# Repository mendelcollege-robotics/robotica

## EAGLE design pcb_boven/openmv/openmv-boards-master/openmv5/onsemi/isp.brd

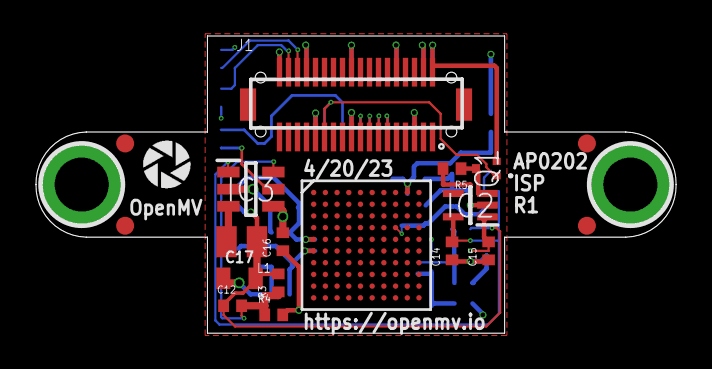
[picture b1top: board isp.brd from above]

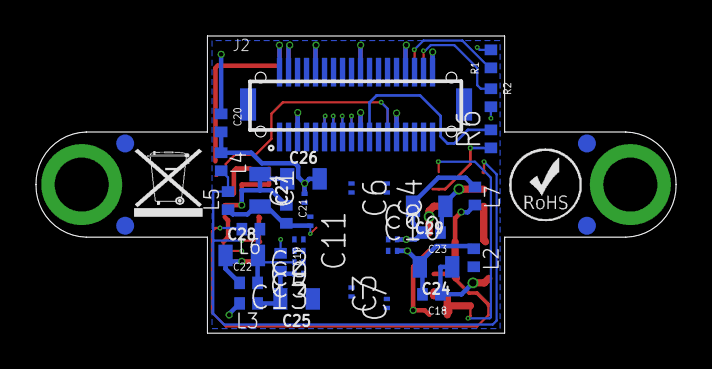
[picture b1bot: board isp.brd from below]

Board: 6 copper layers, 35.6 x 16.5 mm, 61 parts (40 on the bottom side), 56 nets.

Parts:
C1, C2, C3, C4, C5, C6, C7, C8, C9, C10, C11, C13: 0.22uF; C0201
C12: 6.8pF; 0402
C14, C15, C16, C18, C19, C20, C21, C22, C23: 4.7uF; 0402
C17, C24, C25, C26, C27, C28, C29: 22uF; 0805
FD1, FD2, FD3, FD4, FD5, FD6, FD7, FD8: FIDUCIAL1X2; FIDUCIAL-1X2
IC1: AP0202AT2L00XPGA0
IC2: MIC5365-2.8YC5-TR; SOT65P210X110-5N
IC3: TLV62568PDDCR; SOT95P280X110-6N
J1: DF12-36-DS
J2: DF12-36-DP
L1: MAKK2016T2R2M; INDC2016X100N
L2, L3, L4, L5, L6, L7: 100; 0402
M1, M2: 9774030151R
Q1: SSM3J15FV,L3F; SSM3J15FVL3F
R1, R2: 1.5K; R0402
R3, R4, R5: 100K; R0402
R6: 10K; R0402
U$1: WEEE
U$2: ROHS
U$9: OPENMV-LOGO

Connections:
DCMI_CLK: IC1.P$58, J2.12
DCMI_D0: IC1.P$65, J2.31
DCMI_D1: IC1.P$84, J2.29
DCMI_D2: IC1.P$74, J2.35
DCMI_D3: IC1.P$83, J2.28
DCMI_D4: IC1.P$93, J2.26
DCMI_D5: IC1.P$73, J2.33
DCMI_D6: IC1.P$82, J2.24
DCMI_D7: IC1.P$91, J2.22
DCMI_FSIN: IC1.P$63, J2.23
DCMI_HSYNC: IC1.P$64, J2.18
DCMI_MISO: J1.15, J2.15
DCMI_MOSI: J1.17, J2.17
DCMI_PCLK: IC1.P$81, J2.14
DCMI_PWDN: IC1.P$43, J1.25, J2.25, Q1.1
DCMI_PWDN_INT: IC2.3, Q1.3, R5.1
DCMI_RST: J2.21, R6.2
DCMI_SCL: IC1.P$11, J2.32
DCMI_SCLK: J1.13, J2.13
DCMI_SDA: IC1.P$23, J2.34
DCMI_SSEL: J1.11, J2.11
DCMI_VSYNC: IC1.P$72, J2.16
FB: C12.2, IC3.6, R3.1, R4.1
GND: C1.1, C2.1, C3.1, C4.1, C5.1, C6.1, C7.1, C8.1, C9.1, C10.1, C11.1, C13.1, C14.1, C15.1, C16.1, C17.1, C18.1, C19.1, C20.1, C21.1, C22.1, C23.1, C24.1, C25.1, C26.1, C27.1, C28.1, C29.1, IC1.P$1, IC1.P$19, IC1.P$20, IC1.P$22, IC1.P$29, IC1.P$30, IC1.P$32, IC1.P$39, IC1.P$40, IC1.P$44, IC1.P$45, IC1.P$46, IC1.P$48, IC1.P$49, IC1.P$55, IC1.P$56, IC1.P$57, IC1.P$61, IC1.P$69, IC1.P$100, IC2.2, IC3.2, J1.5, J1.19, J1.27, J2.5, J2.19, J2.27, R4.2, R5.2
RESET_N: IC1.P$54, IC3.5, R6.1
SENSOR_CLK: IC1.P$13, J1.12
SENSOR_D0: IC1.P$4, J1.3
SENSOR_D1: IC1.P$15, J1.1
SENSOR_D2: IC1.P$36, J1.9
SENSOR_D3: IC1.P$26, J1.7
SENSOR_D4: IC1.P$16, J1.31
SENSOR_D5: IC1.P$6, J1.29
SENSOR_D6: IC1.P$47, J1.35
SENSOR_D7: IC1.P$37, J1.28
SENSOR_D8: IC1.P$27, J1.26
SENSOR_D9: IC1.P$17, J1.33
SENSOR_D10: IC1.P$7, J1.24
SENSOR_D11: IC1.P$18, J1.22
SENSOR_FSIN: IC1.P$25, J1.23
SENSOR_HSYNC: IC1.P$8, J1.18
SENSOR_PCLK: IC1.P$28, J1.14
SENSOR_RST: IC1.P$35, J1.21
SENSOR_SCL: IC1.P$14, J1.32, R1.1
SENSOR_SDA: IC1.P$3, J1.34, R2.1
SENSOR_VSYNC: IC1.P$10, J1.16
SW: IC3.3, L1.2
VCC: C15.2, C16.2, IC2.1, IC3.4, J1.2, J1.10, J1.20, J1.30, J1.36, J2.2, J2.10, J2.20, J2.30, J2.36, L2.2, L3.2, Q1.2, R1.2, R2.2
VDD: C6.2, C7.2, C8.2, C9.2, C23.2, C29.2, IC1.P$5, IC1.P$41, IC1.P$60, IC1.P$95, L7.1
VDDA: J1.4, J2.4
VDDIO_H: C2.2, C3.2, C4.2, C13.2, C19.2, C25.2, IC1.P$2, IC1.P$34, IC1.P$50, IC1.P$68, IC1.P$80, IC1.P$92, L3.1
VDDIO_OTPM: C10.2, C18.2, C24.2, IC1.P$51, L2.1
VDDIO_REG: C14.2, IC2.5, IC3.1, L4.2, L5.2
VDDIO_S: C1.2, C20.2, C26.2, IC1.P$9, L4.1
VDD_PHY: C11.2, C21.2, C27.2, IC1.P$38, L5.1
VDD_PLL: C5.2, C22.2, C28.2, IC1.P$70, L6.1
VDD_REG: C12.1, C17.2, L1.1, L6.2, L7.2, R3.2

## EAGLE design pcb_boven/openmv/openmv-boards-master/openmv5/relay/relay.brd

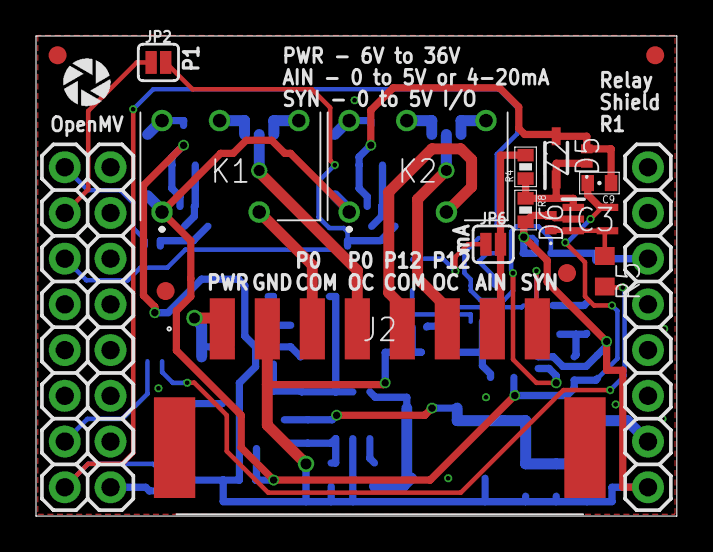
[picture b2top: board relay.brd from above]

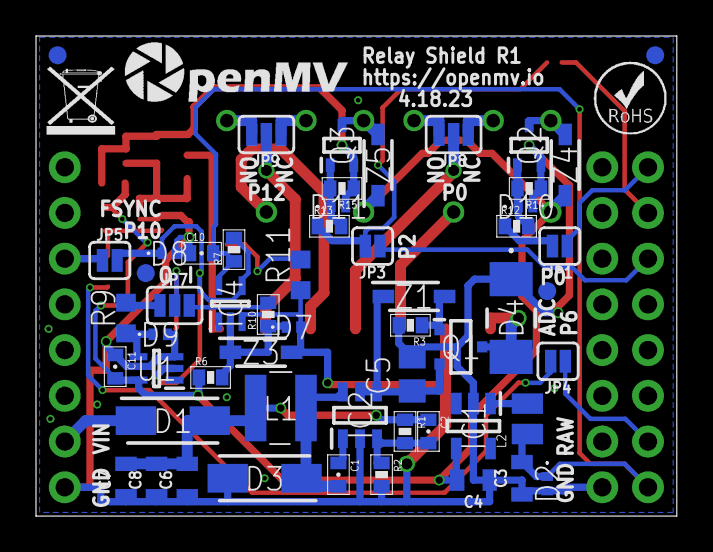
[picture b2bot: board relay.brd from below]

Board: 2 copper layers, 35.6 x 26.7 mm, 77 parts (58 on the bottom side), 42 nets.

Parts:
C1, C9, C10, C11: 0.1uF; 0402-CAP
C2: 100pF; 0402-CAP
C3, C4, C6, C7, C8: 22uF; 0805
C5: 10uF; C0805
D1, D3: FM240A; DIOM5025X231N
D2, D5, D6, D7, D8, D9, D10, D11: CPDQT5V0HE-HF; CPDQT5V0HEHF
D4: SMAJ40CAE3_TR13; SMAJ40CAE3TR13
FD1, FD2, FD3, FD4, FD5, FD6, FD7, FD8: FIDUCIAL1X2; FIDUCIAL-1X2
IC1: TPS613222ADBVR; SOT95P280X145-5N
IC2: AP64060WU-7; SOT95P280X100-6N
IC3: LM321LVIDCKR; SOT65P210X110-5N
IC4: 74LVC1G07GW,125; SOT65P212X110-5N
J1: OPENMV5-TOP
J2: 1771088
JP1, JP3, JP4, JP5: JUMPER-SMT_2_NC_PASTE_SILK; SMT-JUMPER_2_NC_PASTE_SILK
JP2, JP6: JUMPER-SMT_2_NO_SILK; SMT-JUMPER_2_NO_SILK
JP7, JP8, JP9: JUMPER-SMT_3_1-NC_PASTE_SILK; SMT-JUMPER_3_1-NC_PASTE_SILK
K1, K2: IMC03TS
L1: NRS4018T100MDGJ
L2: MAKK2016T2R2M; INDC2016X100N
Q1: SSM3J356R,LF; SOTFL95P240X88-3N
Q2, Q3: 2N7002KW_R1_00001; SOT65P210X110-3N
R1: 133K; 0402-RES
R2: 22.1K; 0402-RES
R3, R6, R7, R8, R14, R15: 100K; 0402-RES
R4: 51K; 0402-RES
R5, R9: 470; R0603
R10, R12, R13: 10K; 0402-RES
R11: 240; R0603
U1: 74LVC1G17SE-7; SOT65P210X110-5N
U$1: WEEE
U$2: ROHS
U$3: OMV-LOGO
U$9: OPENMV-LOGO
Z1, Z3, Z4, Z5: MMSZ5231B-7-F; SOD3716X145N
Z2: DNP; SOD2512X110N

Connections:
AIN: J2.7, JP6.2, R4.2
AIN_INT: D5.1, IC3.1, R4.1, R8.1, Z2.1
AIN_OUT: D6.1, IC3.3, IC3.4, R5.1
AIN_S: JP6.1, R11.2
EXT_VIN: D4.2, J2.1, Q1.3
EXT_VIN_BST: C1.1, IC2.1
EXT_VIN_FB: C2.2, IC2.3, R1.2, R2.1
EXT_VIN_G: Q1.1, R3.1, Z1.2
EXT_VIN_INT: C5.1, IC2.4, IC2.5, Q1.2, Z1.1
EXT_VIN_OUT: C2.1, C6.2, C7.2, C8.2, D1.2, L1.2, R1.1
EXT_VIN_SW: C1.2, D3.1, IC2.6, L1.1
GND: C3.1, C4.1, C5.2, C6.1, C7.1, C8.1, C9.1, C10.1, C11.1, D2.2, D3.2, D4.1, D5.2, D6.2, D7.2, D8.2, D9.2, D10.2, D11.2, IC1.2, IC2.2, IC3.2, IC4.3, J1.9, J1.24, J2.2, Q2.2, Q3.2, R2.2, R3.2, R8.2, R11.1, R14.1, R15.1, U1.3, Z2.2, Z3.2
P0: JP1.2, R12.1
P0_COM: J2.3, K1.3
P0_CONTROL: D10.1, Q2.1, R12.2, R14.2
P0_INT: J1.1, JP1.1
P0_N: J2.4, JP8.2
P0_NC: JP8.1, K1.7
P0_NO: JP8.3, K1.5
P0_RELAY: K1.8, Q2.3, Z4.2
P1_INT: J1.2, JP2.1
P2_INT: J1.3, JP3.1
P6_ADC: JP4.2, R5.2
P6_ADC_INT: J1.7, JP4.1
P10_FSYNC: D8.1, IC4.4, JP5.2, R7.2, U1.2
P10_FSYNC_INT: J1.14, JP5.1
P12: JP2.2, JP3.2, R13.1
P12_COM: J2.5, K2.3
P12_CONTROL: D11.1, Q3.1, R13.2, R15.2
P12_N: J2.6, JP9.2
P12_NC: JP9.1, K2.7
P12_NO: JP9.3, K2.5
P12_RELAY: K2.8, Q3.3, Z5.2
SW: IC1.1, L2.2
SYNC: J2.8, JP7.2
SYNC_IN: JP7.3, R10.2
SYNC_IN_INT: D7.1, IC4.2, R6.2, R10.1, Z3.1
SYNC_OUT: JP7.1, R9.2
SYNC_OUT_INT: D9.1, R9.1, U1.4
VCC: C3.2, C10.2, D2.1, IC4.5, J1.8, L2.1, R7.1
VIN: D1.1, J1.10
V_BATT: C4.2, C9.2, C11.2, IC1.4, IC3.5, K1.1, K2.1, R6.1, U1.5, Z4.1, Z5.1

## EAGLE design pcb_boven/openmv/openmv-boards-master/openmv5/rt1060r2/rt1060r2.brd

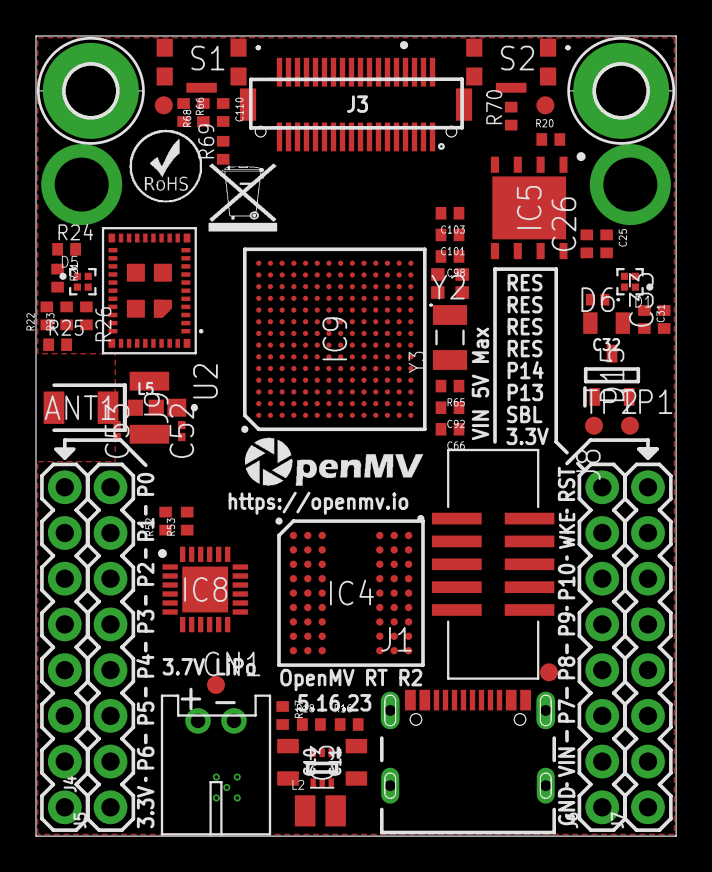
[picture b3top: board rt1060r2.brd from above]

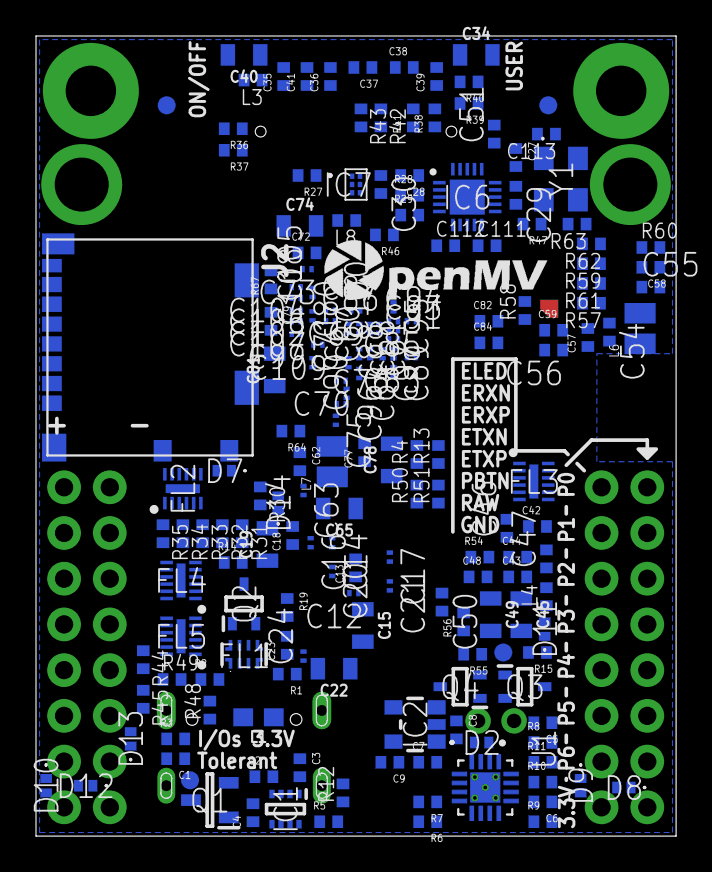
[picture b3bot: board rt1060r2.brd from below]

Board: 8 copper layers, 35.6 x 44.4 mm, 258 parts (187 on the bottom side), 225 nets, no tracks yet.

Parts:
ANT1: AMCA31-2R450G-S1F-T3; ANTC3216X140N
C1: 1nF; 0402
C2, C3, C4, C5, C6, C7, C8, C9, C13, C18, C23, C25, C27, C28, C31, C35, C36, C37, C38, C39, C41, C42, C43, C44, C48, C57, C58, C59, C62, C66, C72, C77, C79, C82, C84, C92, C98, C101, C103, C110, C112, C113: 4.7uF; 0402
C10, C11, C15, C19, C22, C32, C34, C40, C45, C49, C65, C74, C78, C81: 22uF; 0805
C12, C14, C16, C17, C20, C21, C24, C60, C61, C63, C64, C67, C68, C69, C70, C71, C73, C75, C76, C80, C83, C85, C86, C87, C88, C89, C90, C91, C93, C94, C95, C96, C97, C99, C100, C102, C104, C109: 0.22uF; C0201
C26, C29, C30, C33, C46, C47, C50, C51, C54, C55, C56, C111: 0.1uF; 0402
C52: GRM0335C1H1R5BA01D; CAPC0603X33N
C53: DNP; CAPC0603X33N
C105, C106: 4.7pF; C0201
C107, C108: 18pF; C0201
CN1: S2B-PH-K-S(LF)(SN); JST-PH-2-THM-RA
D1, D5: UHD1110-FKA-CL1A13R3Q1BBQFMF3; LED_UHD1110-FKA-CL1A13R3Q1BBQFMF3
D2, D6, D7, D8, D9, D10, D11, D12, D13, D14: CPDQT5V0HE-HF; CPDQT5V0HEHF
D15: BAT54CLT3G; SOT96P237X111-3N
FD1, FD2, FD3, FD4, FD5, FD6, FD7, FD8: FIDUCIAL1X2; FIDUCIAL-1X2
FL1: ECMF02-4CMX8; ECMF024CMX8
FL2, FL3, FL4, FL5: EMIF06-1005M12; SON40P150X250X65-13N
H1, H2: MOUNT-PAD-ROUND2.8; 2,8-PAD
IC1: LM66200DRLR; SOTFL50P160X60-8N
IC2: TCR2LF33,LM_CT; TCR2LF33LMCT
IC3: AP61300Z6-7; SOTFL50P162X60-6N
IC4: IS42S16160G-6BL; BGA54C80P9X9_800X800X120
IC5: IS25LP128F-JKLE-TR; SON127P500X595X80-9N
IC6: SE050C1HQ1_Z01SCZ; QFN40P300X300X33-21N
IC7: MXC4005XC
IC8: KSZ8081RNDCA-TR; QFN50P400X400X90-25N
IC9: MIMXRT106FDVL6B; BGA196C65P14X14_1000X1000X143
J1: USB4105-GF-A; GCT_USB4105-GF-A
J2: USD-1040310811; 1040310811
J3: DF12-36-DS
J4, J5, J6, J7: DNP; 1X08
J8: 3221-10-0300-00; CNC_3221-10-0300-00
J9: DNP; 23370191
L1: 100; 0603
L2: MAKK2016T1R0M; INDC2016X100N
L3, L4, L8: 100; 0402
L5: 3.9NH; 0402
L6: MAKK2016T2R2M; INDC2016X100N
L7: MAKK2016T4R7M; INDC2016X100N
M1, M2: 9774030151R
Q1: DMG2301L-7; SOT96P240X110-3N
Q2, Q3, Q4: 2N7002KW_R1_00001; SOT65P210X110-3N
R1, R2, R6, R23: 5.1K; 0402
R3: 1M; 0402
R4, R12, R13, R14, R15, R17, R19, R20, R30, R31, R32, R33, R34, R35, R36, R41, R52, R59, R60, R61, R62, R63, R65, R69: 100K; 0402
R5, R21, R42, R43, R54, R56: 1K; 0402
R7, R8, R22, R24, R25, R26, R37, R38, R46, R47, R57, R58, R66, R68, R70: 10K; 0402
R9: 1.1K; 0402
R10: 46.4K; 0402
R11: 8.2K; 0402
R16: 200K; 0402
R18: 44.2K; 0402
R27, R28, R29: 2.7K; 0402
R39, R40: 4.7K; 0402
R44, R45: 0; 0402
R48, R49, R50, R51: DNP; 0402
R53: 220; 0402
R55: 6.49K; 0402
R64: 30K; 0402
R67: 2.2M; 0402
S1, S2: KMS231GLFS
TP1, TP2: TPTP10R; TP10R
U1: BQ24075RGTR; QFN50P300X300X100-17N
U2: LBEE5KL1DX-883; XCVR_LBEE5KL1DX-TEMP
U$1: WEEE
U$2: ROHS
U$3: OMV-LOGO
U$4: OMV-LOGO-SMALL
Y1: ECS-327MVATX-3-CN-TR3; ECS327MVATX3CNTR3
Y2: XRCGB24M000F3M00R0
Y3: SC32S-7PF20PPM; XTAL_ABS07-32.768KHZ-7-T

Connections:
ANT: C52.1, J9.1, L5.2, U2.41
BAT: C5.2, CN1.1, D2.1, U1.2, U1.3
BT_D_WAKE: IC9.L5, U2.39
BT_H_WAKE: IC9.H14, R58.1, U2.38
BT_REG_ON: IC9.F13, R47.1, U2.14
BT_UART_CTS: IC9.L12, U2.5
BT_UART_RTS: IC9.K12, U2.4
BT_UART_RX: IC9.C9, U2.3
BT_UART_TX: IC9.B9, U2.2
CC1: J1.A5, R1.1
CC2: J1.B5, R2.1
CHG: R6.1, R13.1, R51.2, U1.9
C_VOUT: C111.1, C112.2, IC6.15, IC6.18
DCDC_LP: IC9.M1, IC9.M2, L7.2
DCDC_PSWITCH: C96.1, IC9.K3, R64.1
DCMI_CLK: IC9.B14, J3.12
DCMI_D0: IC9.J14, J3.31
DCMI_D1: IC9.G12, J3.29
DCMI_D2: IC9.H11, J3.35
DCMI_D3: IC9.H12, J3.28
DCMI_D4: IC9.J13, J3.26
DCMI_D5: IC9.L13, J3.33
DCMI_D6: IC9.G14, J3.24
DCMI_D7: IC9.F11, J3.22, R46.1
DCMI_FSIN: J3.23, R42.1
DCMI_HSYNC: IC9.L10, J3.18
DCMI_MISO: IC9.E7, J3.15
DCMI_MOSI: IC9.E8, J3.17
DCMI_PCLK: IC9.D13, J3.14
DCMI_PWDN: IC9.C11, J3.25, R38.1
DCMI_RST: IC9.B11, J3.21, R37.1
DCMI_SCL: IC9.J11, J3.32, R39.1
DCMI_SCLK: IC9.D8, J3.13
DCMI_SDA: IC9.K11, J3.34, R40.1
DCMI_SSEL: IC9.D7, J3.11, R36.1
DCMI_VSYNC: IC9.D14, J3.16
D_N: FL1.3, J1.A7, J1.B7
D_P: FL1.2, J1.A6, J1.B6
EN: IC3.5, Q4.3, R17.1
ETH_INT: IC8.18, IC9.C10, R54.1
ETH_LED: IC8.23, R53.1
ETH_MDC: IC8.11, IC9.A7
ETH_MDIO: IC8.10, IC9.C7, R56.1
ETH_RST: C42.2, IC8.24, IC9.D10, R52.1
ETH_RXD0: IC8.13, IC9.E12
ETH_RXD1: IC8.12, IC9.D12
ETH_RXDV: IC8.15, IC9.C12
ETH_RXERR: IC8.17, IC9.C13
ETH_TXCLK: IC8.8, IC9.B13
ETH_TXD0: IC8.20, IC9.B12
ETH_TXD1: IC8.21, IC9.A12
ETH_TXEN: IC8.19, IC9.A13
ETH_VDDA_3.3: C43.2, C45.1, C46.1, IC8.2, L4.1
ETH_VDD_1.2: C44.2, C47.1, IC8.1
FB: IC3.1, R16.1, R18.2
FEED: ANT1.1, C53.1, L5.1
GND: C1.1, C2.1, C3.1, C4.1, C5.1, C6.1, C7.1, C8.1, C9.1, C10.2, C11.2, C12.1, C13.2, C14.2, C15.2, C16.2, C17.2, C18.1, C19.1, C20.2, C21.2, C22.2, C23.2, C24.1, C25.1, C26.2, C27.1, C28.1, C29.2, C30.2, C31.1, C32.2, C33.2, C34.2, C35.1, C36.1, C37.1, C38.1, C39.1, C40.2, C41.1, C42.1, C43.1, C44.1, C45.2, C46.2, C47.2, C48.1, C49.2, C50.2, C51.2, C52.2, C53.2, C54.2, C55.2, C56.2, C57.1, C58.1, C59.1, C60.2, C61.2, C62.1, C63.2, C64.2, C65.1, C66.1, C67.2, C68.2, C69.2, C70.2, C71.2, C72.1, C73.2, C74.1, C75.2, C76.2, C77.1, C78.1, C79.1, C80.2, C81.1, C82.2, C83.1, C84.2, C85.1, C86.2, C87.2, C88.1, C89.1, C90.2, C91.1, C92.1, C93.1, C94.1, C95.1, C96.2, C97.1, C98.1, C99.2, C100.1, C101.1, C102.2, C103.1, C104.2, C105.2, C106.2, C107.2, C108.2, C109.2, C110.1, C111.2, C112.1, C113.1, CN1.2, D2.2, D6.2, D7.2, D8.2, D9.2, D10.2, D11.2, D12.2, D13.2, D14.2, FL1.5, FL1.8, FL2.13, FL3.13, FL4.13, FL5.13, IC1.1, IC1.4, IC1.5, IC2.2, IC3.2, IC4.A1, IC4.A3, IC4.B7, IC4.C3, IC4.D7, IC4.E3, IC4.J1, IC5.4, IC5.9, IC6.19, IC6.21, IC7.3, IC8.22, IC8.25, IC9.A1, IC9.A14, IC9.B5, IC9.B10, IC9.E2, IC9.E13, IC9.G7, IC9.G8, IC9.H7, IC9.H8, IC9.J7, IC9.J8, IC9.K2, IC9.K6, IC9.K9, IC9.K13, IC9.L9, IC9.N1, IC9.N2, IC9.N5, IC9.N8, IC9.P1, IC9.P14, J1.A1_B12, J1.B1_A12, J2.CD$2, J2.G$1, J2.G$2, J2.G$3, J2.G$4, J2.P$6, J3.5, J3.19, J3.27, J5.1, J7.1, J8.3, J8.5, J9.2, J9.3, Q1.1, R1.2, R2.2, R3.2, R8.2, R9.2, R10.2, R11.2, R18.1, R37.2, R47.2, R55.2, R67.2, S1.1, S1.5, S2.1, S2.5, TP2.TP, U1.4, U1.6, U1.8, U1.15, U1.17, U2.1, U2.12, U2.19, U2.21, U2.29, U2.32, U2.33, U2.35, U2.40, U2.42, U2.43, U2.44, U2.45, U2.46, Y1.2, Y2.2, Y2.4
ILIM: R9.1, U1.12
INT_I2C_INT: IC7.4, IC9.D11, R29.1
INT_I2C_SCL: IC6.10, IC7.1, IC9.C8, R27.1
INT_I2C_SDA: IC6.9, IC7.5, IC9.B8, R28.1
ISET: R11.1, U1.16
JTAG_TCK: FL5.5, IC9.F12
JTAG_TCK_INT: FL5.8, J8.4
JTAG_TDI: FL5.3, IC9.F14, R50.1
JTAG_TDI_INT: FL5.10, R44.1, R48.1
JTAG_TDI_INT_UNUSED: J8.8, R48.2
JTAG_TDO: FL5.4, IC9.G13
JTAG_TDO_INT: FL5.9, J8.6
JTAG_TMS: FL5.6, IC9.E14
JTAG_TMS_INT: FL5.7, J8.2
JTAG_TRSTB: FL5.1, IC9.G10, R51.1
JTAG_TRSTB_INT: FL5.12, R45.1, R49.1
JTAG_TRSTB_INT_UNUSED: J8.9, R49.2
LED_B: IC9.C14, R21.1, R24.1
LED_B_INT: D5.1, R21.2
LED_CHG: D1.3, R6.2
LED_G: IC9.A10, R22.1, R25.1
LED_G_INT: D5.2, R22.2
LED_PGOOD: D1.2, R7.2
LED_R: IC9.D9, R23.1, R26.1
LED_R_INT: D5.3, R23.2
LED_ST: D1.1, R5.2
LPO_IN: U2.37, Y1.3
MDI_LED: J5.8, R53.2
MDI_RX_N: IC8.3, J5.7
MDI_RX_P: IC8.4, J5.6
MDI_TX_N: IC8.5, J5.5
MDI_TX_P: IC8.6, J5.4
NVCC_PLL: C101.2, C102.1, IC9.P10
ONOFF: IC9.M6, Q3.2, R70.1
ONOFF_BUTTON: R70.2, S2.2, S2.3, S2.4
P0_MOSI: FL3.1, IC9.H10
P0_MOSI_INT: FL3.12, J4.8
P1_MISO: FL3.2, IC9.M11
P1_MISO_INT: FL3.11, J4.7
P2_SCLK: FL3.3, IC9.M14
P2_SCLK_INT: FL3.10, J4.6
P3_NSS: FL3.4, IC9.G11
P3_NSS_INT: FL3.9, J4.5
P4_SCL: FL3.5, IC9.K14
P4_SCL_INT: FL3.8, J4.4
P5_SDA: FL3.6, IC9.L14
P5_SDA_INT: FL3.7, J4.3
P6_ADC: FL4.1, IC9.M12
P6_ADC_INT: FL4.12, J4.2
P7_PWM: FL4.2, IC9.A8
P7_PWM_INT: FL4.11, J7.3
P8_PWM: FL4.3, IC9.A9
P8_PWM_INT: FL4.10, J7.4
P9_PWM: FL4.4, IC9.A11
P9_PWM_INT: FL4.9, J7.5
P10_PWM: FL4.5, R43.1
P10_PWM_INT: FL4.8, J7.6
P11_WAKEUP: FL4.6, Q2.3, R14.1
P11_WAKEUP_INT: FL4.7, J7.7
P12_RST_N: C109.1, FL5.2, IC9.M7, R65.2
P12_RST_N_EXT: FL5.11, J7.8, J8.10
P13: J6.3, R45.2
P14: J6.4, R44.2
PGOOD: IC9.P2, R7.1, R12.1, U1.7
PMIC_ONOFF: D11.1, J5.3, Q3.3, R15.1
PMIC_ON_REQ: IC9.K7, Q4.2
PMIC_STBY_REQ: IC9.L7, R69.1
PWM_FSIN: IC9.M5, R41.1, R42.2, R43.2
P_FLASH_CE: IC5.1, IC9.L3, R20.2
P_FLASH_IO0: IC5.5, IC9.P3
P_FLASH_IO1: IC5.2, IC9.N4
P_FLASH_IO2: IC5.3, IC9.P4
P_FLASH_IO3: IC5.7, IC9.P5
P_FLASH_SCK: IC5.6, IC9.L4
RAW: C7.2, C8.2, C10.1, D9.1, IC2.1, IC2.3, IC3.3, J5.2, R14.2, R15.2, R17.2, U1.5, U1.10, U1.11
REXT: IC8.9, R55.1
RTC_XTALI: C108.1, IC9.N9, Y3.2
RTC_XTALO: C107.1, IC9.P9, Y3.1
SBL: D13.1, J6.2, R46.2
SDRAM_A0: IC4.H7, IC9.C2
SDRAM_A1: IC4.H8, IC9.G1
SDRAM_A2: IC4.J8, IC9.G3
SDRAM_A3: IC4.J7, IC9.H1
SDRAM_A4: IC4.J3, IC9.A6
SDRAM_A5: IC4.J2, IC9.B6
SDRAM_A6: IC4.H3, IC9.B1
SDRAM_A7: IC4.H2, IC9.A5
SDRAM_A8: IC4.H1, IC9.A4
SDRAM_A9: IC4.G3, IC9.B2
SDRAM_A10: IC4.H9, IC9.G2
SDRAM_A11: IC4.G2, IC9.B4
SDRAM_A12: IC4.G1, IC9.A3
SDRAM_BA0: IC4.G7, IC9.C1
SDRAM_BA1: IC4.G8, IC9.F1
SDRAM_CAS: IC4.F7, IC9.D3
SDRAM_CKE: IC4.F3, IC9.A2
SDRAM_CLK: IC4.F2, IC9.B3
SDRAM_CS: IC4.G9, IC9.E1, R19.2
SDRAM_DQ0: IC4.A8, IC9.E3
SDRAM_DQ1: IC4.B9, IC9.F3
SDRAM_DQ2: IC4.B8, IC9.F4
SDRAM_DQ3: IC4.C9, IC9.G4
SDRAM_DQ4: IC4.C8, IC9.F2
SDRAM_DQ5: IC4.D9, IC9.G5
SDRAM_DQ6: IC4.D8, IC9.H5
SDRAM_DQ7: IC4.E9, IC9.H4
SDRAM_DQ8: IC4.E1, IC9.C6
SDRAM_DQ9: IC4.D2, IC9.C5
SDRAM_DQ10: IC4.D1, IC9.D5
SDRAM_DQ11: IC4.C2, IC9.C4
SDRAM_DQ12: IC4.C1, IC9.D4
SDRAM_DQ13: IC4.B2, IC9.E5
SDRAM_DQ14: IC4.B1, IC9.C3
SDRAM_DQ15: IC4.A2, IC9.E4
SDRAM_DQMH: IC4.F1, IC9.D6
SDRAM_DQML: IC4.E8, IC9.H3
SDRAM_RAS: IC4.F8, IC9.D2
SDRAM_WE: IC4.F9, IC9.D1
SD_CD: D7.1, IC9.L11, J2.CD$1, R30.1
SD_CLK: FL2.4, IC9.J3
SD_CLK_INT: FL2.9, J2.P$5
SD_CMD: FL2.3, IC9.J4, R33.1
SD_CMD_INT: FL2.10, J2.P$3
SD_DAT0: FL2.5, IC9.J1, R32.1
SD_DAT0_INT: FL2.8, J2.P$7
SD_DAT1: FL2.6, IC9.K1, R31.1
SD_DAT1_INT: FL2.7, J2.P$8
SD_DAT2: FL2.1, IC9.H2, R35.1
SD_DAT2_INT: FL2.12, J2.P$1
SD_DAT3: FL2.2, IC9.J2, R34.1
SD_DAT3_INT: FL2.11, J2.P$2
SHELL_GND: C1.2, J1.S1, J1.S2, J1.S3, J1.S4, R3.1
SNVS_BAT: D15.2, TP1.TP
SR_VLX: L6.1, U2.34
ST: IC1.8, R4.1, R5.1, R50.2
SW: IC3.4, L2.1
SWITCH: R66.1, R68.2, S1.2, S1.3, S1.4
SWITCH_OUT: C110.2, R68.1, R69.2
TMR: R10.1, U1.14
TS: R8.1, U1.1
USB_D_N: FL1.6, IC9.M8
USB_D_P: FL1.7, IC9.L8
USB_VBUS: FL1.4, J1.A4_B9, J1.B4_A9, L1.1
VBUS: C2.2, C90.1, C92.2, FL1.1, IC1.3, IC9.N6, L1.2
VCC: C11.1, C12.2, C13.1, C14.1, C15.1, C16.1, C17.1, C18.2, C19.2, C20.1, C21.1, C22.1, C23.1, C24.2, C25.2, C26.1, C27.2, C28.2, C29.1, C30.1, C31.2, C32.1, C33.1, C34.1, C35.2, C36.2, C37.2, C38.2, C39.2, C48.2, C49.1, C50.1, C51.1, C55.1, C56.1, C58.2, C59.2, C66.2, C67.1, C69.1, C70.1, C71.1, C75.1, C76.1, C77.2, C78.2, C82.1, C83.2, C84.1, C85.2, C88.2, C95.2, C103.2, C104.1, C113.2, D1.4, D5.4, D6.1, D8.1, D12.1, D14.1, IC3.6, IC4.A7, IC4.A9, IC4.B3, IC4.C7, IC4.D3, IC4.E7, IC4.J9, IC5.8, IC6.11, IC6.12, IC7.6, IC8.14, IC9.E6, IC9.E9, IC9.F5, IC9.F10, IC9.J6, IC9.J10, IC9.K4, IC9.K5, IC9.L1, IC9.L2, IC9.P12, J2.P$4, J3.2, J3.10, J3.20, J3.30, J3.36, J4.1, J6.1, J8.1, L2.2, L3.2, L4.2, L8.2, R4.2, R12.2, R13.2, R16.2, R19.1, R20.1, R24.2, R25.2, R26.2, R27.2, R28.2, R29.2, R30.2, R31.2, R32.2, R33.2, R34.2, R35.2, R36.2, R38.2, R39.2, R40.2, R41.2, R52.2, R54.2, R56.2, R57.2, R58.2, R59.2, R60.2, R61.2, R62.2, R63.2, R64.2, R65.1, R66.2, U2.30, U2.36, Y1.1, Y1.4
VCC_SOC: C60.1, C61.1, C62.2, C63.1, C64.1, C65.2, C68.1, C89.2, C91.2, C93.2, C94.2, C97.2, C100.2, IC9.F6, IC9.F7, IC9.F8, IC9.F9, IC9.G6, IC9.G9, IC9.H6, IC9.H9, IC9.J5, IC9.J9, L7.1
VDDA: C40.1, C41.2, J3.4, L3.1
VDDA_ADC_3P3: C72.2, C73.1, C74.2, IC9.N14, L8.1
VDD_HIGH_CAP: C98.2, C99.1, IC9.P8
VDD_SNVS: C9.2, D15.1, IC2.5
VDD_SNVS_CAP: C87.1, IC9.M10
VDD_SNVS_CPU: C86.1, D15.3, IC9.M9, Q2.1, Q3.1, Q4.1
VDD_USB_CAP: C79.2, C80.1, C81.2, IC9.K8
VIN: D10.1, J7.2, Q1.3
VIN_INT: C4.2, IC1.6, Q1.2
VIN_LDO: C54.1, C57.2, L6.2, U2.31
V_BATT: C3.2, C6.2, IC1.2, IC1.7, U1.13
WAKEUP: IC9.L6, Q2.2
WIFI_CLK: IC9.M13, U2.20
WIFI_CMD: IC9.H13, R63.1, U2.22
WIFI_D0: IC9.M4, R62.1, U2.24
WIFI_D1: IC9.M3, R61.1, U2.26
WIFI_D2: IC9.J12, R60.1, U2.23
WIFI_D3: IC9.K10, R59.1, U2.25
WL_H_WAKE: IC9.E11, R57.1, U2.27
WL_REG_ON: IC9.E10, U2.28
XTALI: C106.1, IC9.P11, R67.1, Y2.3
XTALO: C105.1, IC9.N11, Y2.1

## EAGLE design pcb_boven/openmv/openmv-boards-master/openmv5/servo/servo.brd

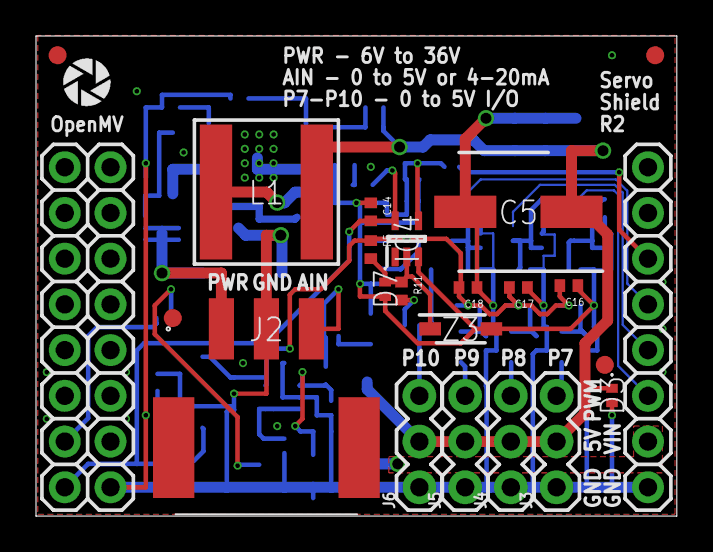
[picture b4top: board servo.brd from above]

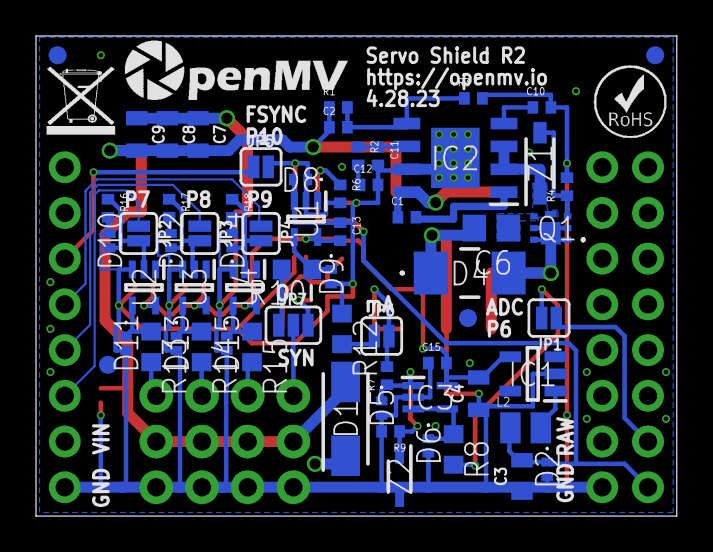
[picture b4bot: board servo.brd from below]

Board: 2 copper layers, 35.6 x 26.7 mm, 90 parts (67 on the bottom side), 40 nets.

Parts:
C1, C13, C14, C15, C16, C17, C18: 0.1uF; 0402
C2: 100pF; 0402
C3, C4, C7, C8, C9: 22uF; 0805
C5: EDK227M010A9HAA; CAPAE660X800N
C6: 10uF; C0805
C10: 10nF; 0402
C11: 33pF; 0402
C12: 2.7nF; 0402
D1: FM240A; DIOM5025X231N
D2, D3, D5, D6, D7, D8, D9, D10, D11, D12, D13, D14, D15: CPDQT5V0HE-HF; CPDQT5V0HEHF
D4: SMAJ40CAE3_TR13; SMAJ40CAE3TR13
FD1, FD2, FD3, FD4, FD5, FD6, FD7, FD8: FIDUCIAL1X2; FIDUCIAL-1X2
IC1: TPS613222ADBVR; SOT95P280X145-5N
IC2: AP64501SP-13; SOIC127P600X163-9N
IC3: LM321LVIDCKR; SOT65P210X110-5N
IC4: 74LVC1G07GW,125; SOT65P212X110-5N
J1: OPENMV5-TOP
J2: 1771033
J3, J4, J5, J6: 1X03
JP1, JP2, JP3, JP4, JP5: JUMPER-SMT_2_NC_PASTE_SILK; SMT-JUMPER_2_NC_PASTE_SILK
JP6: JUMPER-SMT_2_NO_SILK; SMT-JUMPER_2_NO_SILK
JP7: JUMPER-SMT_3_1-NC_PASTE_SILK; SMT-JUMPER_3_1-NC_PASTE_SILK
L1: NR8040T3R6N
L2: MAKK2016T2R2M; INDC2016X100N
Q1: BUK6D120-60PX; BUK6D12060PX
R1: 133K; 0402
R2: 15.8K; 0402
R3: 22.1K; 0402
R4, R5, R6, R9, R16, R17, R18: 100K; 0402
R7: 51K; 0402
R8, R10, R13, R14, R15: 470; R0603
R11: 10K; 0402
R12: 240; R0603
U1, U2, U3, U4: 74LVC1G17SE-7; SOT65P210X110-5N
U$1: WEEE
U$2: ROHS
U$3: OMV-LOGO
U$9: OPENMV-LOGO
Z1, Z3: MMSZ5231B-7-F; SOD3716X145N
Z2: DNP; SOD2512X110N

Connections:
AIN: J2.3, JP6.2, R7.2
AIN_INT: D5.1, IC3.1, R7.1, R9.1, Z2.1
AIN_OUT: D6.1, IC3.3, IC3.4, R8.1
AIN_S: JP6.1, R12.2
EXT_VIN: D4.2, J2.1, Q1.1, Q1.2, Q1.5, Q1.6, Q1.7
EXT_VIN_BST: C1.2, IC2.1
EXT_VIN_COMP: C11.1, IC2.6, R2.1
EXT_VIN_COMP_CAP: C12.1, R2.2
EXT_VIN_FB: C2.2, IC2.5, R1.2, R3.1
EXT_VIN_G: Q1.3, R4.1, Z1.2
EXT_VIN_INT: C6.1, IC2.2, IC2.3, Q1.4, Q1.8, Z1.1
EXT_VIN_OUT: C2.1, C5.1, C7.2, C8.2, C9.2, D1.2, D3.1, J3.2, J4.2, J5.2, J6.2, L1.2, R1.1
EXT_VIN_SS: C10.1, IC2.4
EXT_VIN_SW: C1.1, IC2.8, L1.1
GND: C3.1, C4.1, C5.2, C6.2, C7.1, C8.1, C9.1, C10.2, C11.2, C12.2, C13.1, C14.1, C15.1, C16.1, C17.1, C18.1, D2.2, D3.2, D4.1, D5.2, D6.2, D7.2, D8.2, D9.2, D10.2, D11.2, D12.2, D13.2, D14.2, D15.2, IC1.2, IC2.7, IC2.9, IC3.2, IC4.3, J1.9, J1.24, J2.2, J3.1, J4.1, J5.1, J6.1, R3.2, R4.2, R9.2, R12.1, R16.2, R17.2, R18.2, U1.3, U2.3, U3.3, U4.3, Z2.2, Z3.2
P6_ADC: JP1.2, R8.2
P6_ADC_INT: J1.7, JP1.1
P7_PWM: D10.1, JP2.2, R16.1, U2.2
P7_PWM_INT: J1.11, JP2.1
P7_PWM_SERVO: J3.3, R13.2
P7_PWM_SERVO_INT: D11.1, R13.1, U2.4
P8_PWM: D12.1, JP3.2, R17.1, U3.2
P8_PWM_INT: J1.12, JP3.1
P8_PWM_SERVO: J4.3, R14.2
P8_PWM_SERVO_INT: D13.1, R14.1, U3.4
P9_PWM: D14.1, JP4.2, R18.1, U4.2
P9_PWM_INT: J1.13, JP4.1
P9_PWM_SERVO: J5.3, R15.2
P9_PWM_SERVO_INT: D15.1, R15.1, U4.4
P10_FSYNC: D8.1, IC4.4, JP5.2, R6.2, U1.2
P10_FSYNC_INT: J1.14, JP5.1
SW: IC1.1, L2.2
SYNC: J6.3, JP7.2
SYNC_IN: JP7.3, R11.2
SYNC_IN_INT: D7.1, IC4.2, R5.2, R11.1, Z3.1
SYNC_OUT: JP7.1, R10.2
SYNC_OUT_INT: D9.1, R10.1, U1.4
VCC: C3.2, C14.2, D2.1, IC4.5, J1.8, L2.1, R6.1
VIN: D1.1, J1.10
V_BATT: C4.2, C13.2, C15.2, C16.2, C17.2, C18.2, IC1.4, IC3.5, R5.1, U1.5, U2.5, U3.5, U4.5

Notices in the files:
parts and their libraries:
SparkFun-Aesthetics: Licensing: Creative Commons ShareAlike 4.0 International - https://creativecommons.org/licenses/by-sa/4.0
